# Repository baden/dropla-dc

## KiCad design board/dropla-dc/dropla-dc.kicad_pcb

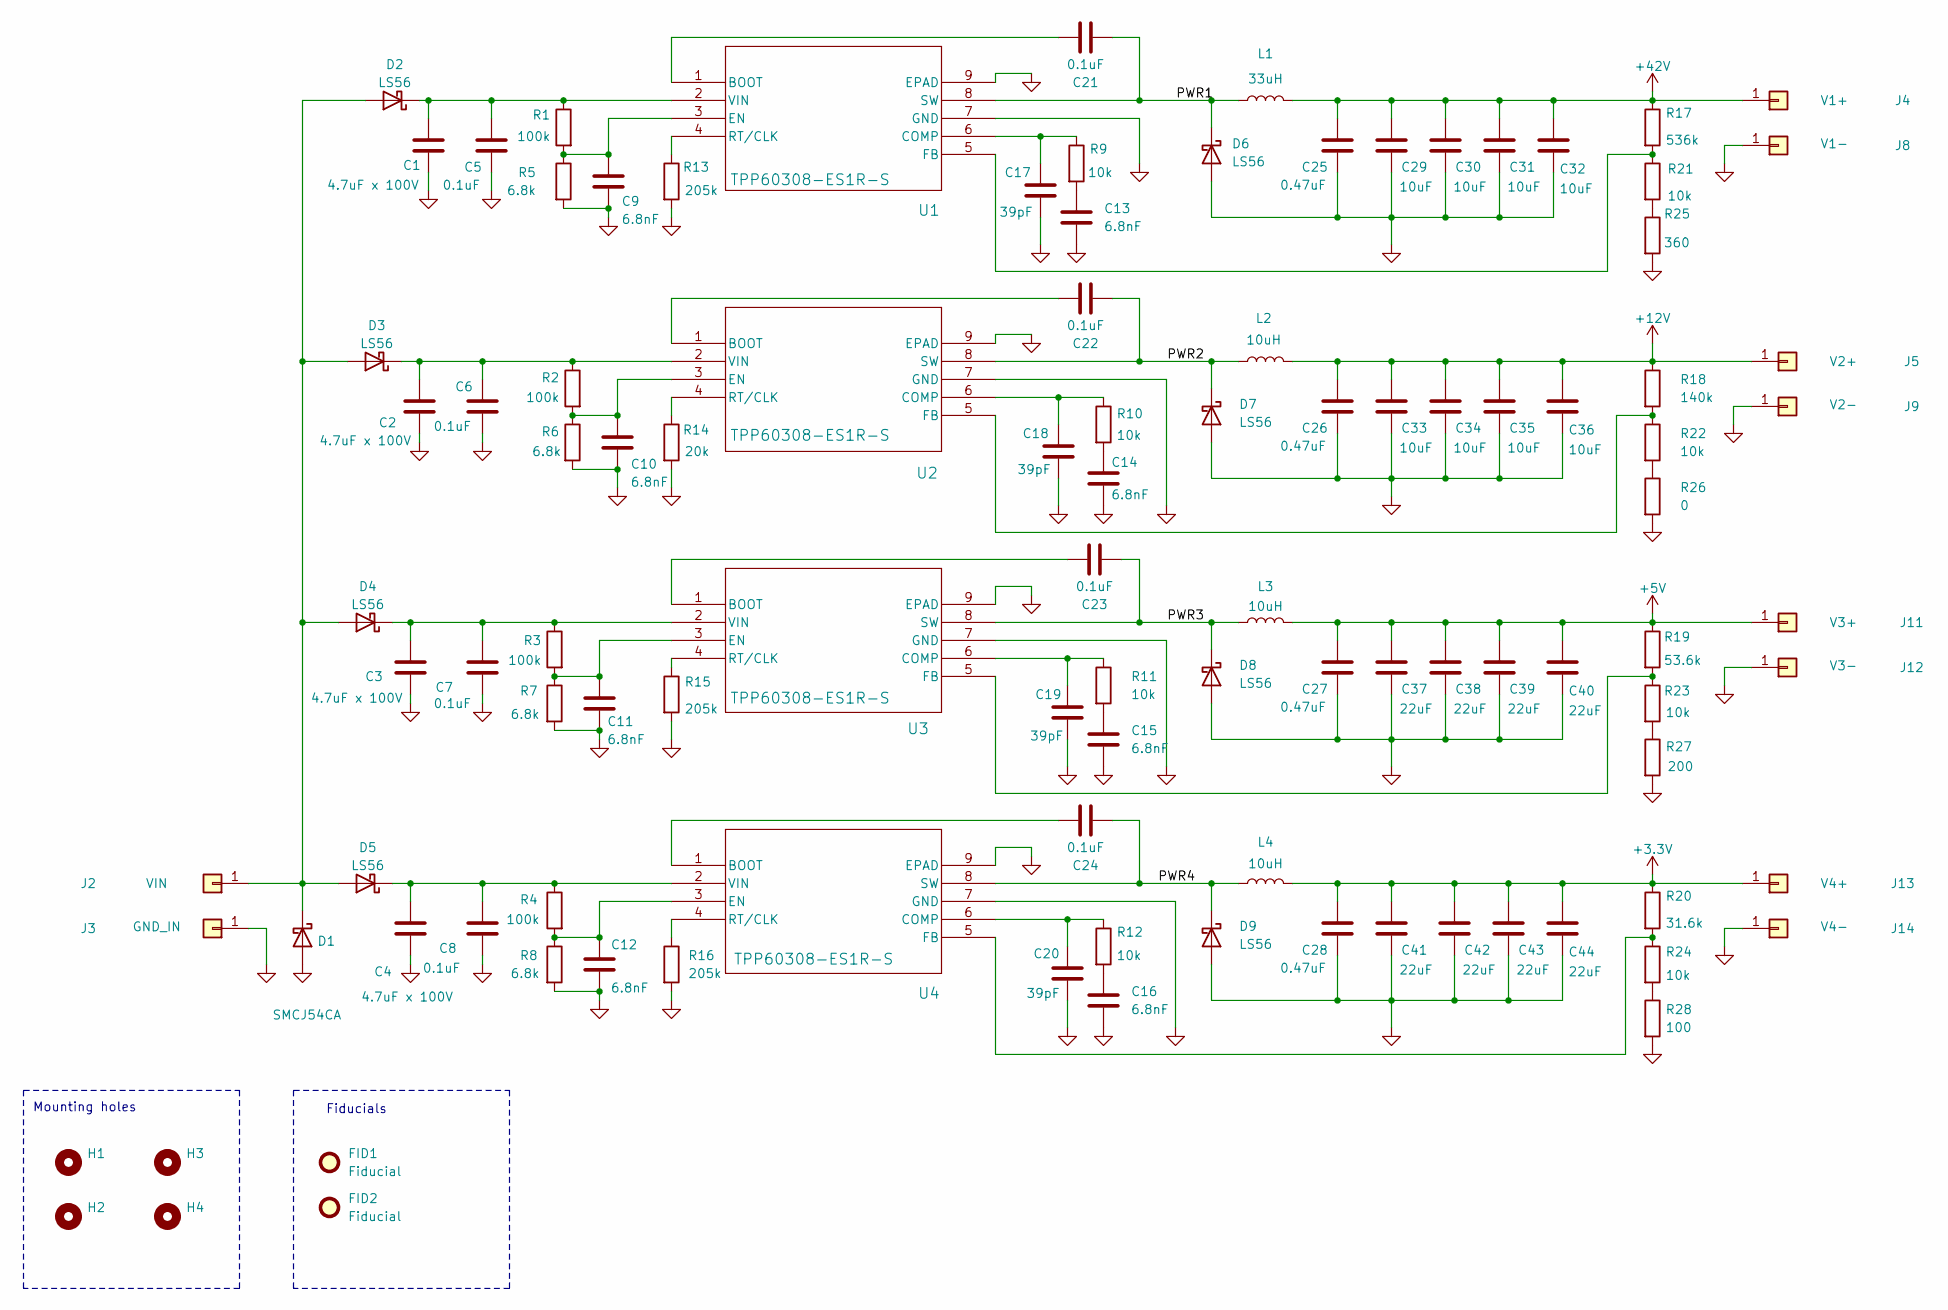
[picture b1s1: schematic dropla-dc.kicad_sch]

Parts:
C1, C2, C3, C4: 4.7uF x 100V; C_1210_3225Metric
C5, C6, C7, C8, C21, C22, C23, C24: 0.1uF; C_0603_1608Metric
C9, C10, C11, C12, C13, C14, C15, C16: 6.8nF; C_0603_1608Metric
C17, C18, C19, C20: 39pF; C_0603_1608Metric
C25, C26, C27, C28: 0.47uF; C_0603_1608Metric
C29, C30, C31, C32, C33, C34, C35, C36: 10uF; C_1206_3216Metric
C37, C38, C39, C40, C41, C42, C43, C44: 22uF; C_1206_3216Metric
D1: SMCJ54CA; D_SMC
D2, D3, D4, D5, D6, D7, D8, D9: LS56; D_SMA
FID1, FID2: Fiducial; Fiducial_1mm_Mask3mm
H1, H2, H3, H4: MountingHole; MountingHole_3.2mm_M3_DIN965
J2: VIN; Pin_D1.1mm_L8.5mm_W2.5mm_FlatFork
J3: GND_IN; Pin_D1.1mm_L8.5mm_W2.5mm_FlatFork
J4: V1+; Pin_D1.1mm_L8.5mm_W2.5mm_FlatFork
J5: V2+; Pin_D1.1mm_L8.5mm_W2.5mm_FlatFork
J8: V1-; Pin_D1.1mm_L8.5mm_W2.5mm_FlatFork
J9: V2-; Pin_D1.1mm_L8.5mm_W2.5mm_FlatFork
J11: V3+; Pin_D1.1mm_L8.5mm_W2.5mm_FlatFork
J12: V3-; Pin_D1.1mm_L8.5mm_W2.5mm_FlatFork
J13: V4+; Pin_D1.1mm_L8.5mm_W2.5mm_FlatFork
J14: V4-; Pin_D1.1mm_L8.5mm_W2.5mm_FlatFork
L1: 33uH; L_TechFuse_SL1040
L2, L3, L4: 10uH; L_Coilcraft_XAL7030-472
R1, R2, R3, R4: 100k; R_0603_1608Metric
R5, R6, R7, R8: 6.8k; R_0603_1608Metric
R9, R10, R11, R12, R21, R22, R23, R24: 10k; R_0603_1608Metric
R13, R15, R16: 205k; R_0603_1608Metric
R14: 20k; R_0603_1608Metric
R17: 536k; R_0603_1608Metric
R18: 140k; R_0603_1608Metric
R19: 53.6k; R_0603_1608Metric
R20: 31.6k; R_0603_1608Metric
R25: 360; R_0603_1608Metric
R26: 0; R_0603_1608Metric
R27: 200; R_0603_1608Metric
R28: 100; R_0603_1608Metric
U1, U2, U3, U4: TPP60308-ES1R-S; SOIC-8-1EP_3.9x4.9mm_P1.27mm_EP2.29x3mm_ThermalVias

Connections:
+3.3V: C28.2, C41.1, C42.1, C43.1, C44.1, J13.1 (Pin_1_1), L4.2, R20.1
+5V: C27.2, C37.1, C38.1, C39.1, C40.1, J11.1 (Pin_1_1), L3.2, R19.1
+12V: C26.2, C33.1, C34.1, C35.1, C36.1, J5.1 (Pin_1_1), L2.2, R18.1
+42V: C25.2, C29.1, C30.1, C31.1, C32.1, J4.1 (Pin_1_1), L1.2, R17.1
/PWR1: C21.2, D6.1 (K), L1.1, U1.8 (SW)
/PWR2: C22.2, D7.1 (K), L2.1, U2.8 (SW)
/PWR3: C23.2, D8.1 (K), L3.1, U3.8 (SW)
/PWR4: C24.2, D9.1 (K), L4.1, U4.8 (SW)
GND: C1.2, C2.2, C3.2, C4.2, C5.1, C6.1, C7.1, C8.1, C9.1, C10.1, C11.1, C12.1, C13.1, C14.1, C15.1, C16.1, C17.1, C18.1, C19.1, C20.1, C25.1, C26.1, C27.1, C28.1, C29.2, C30.2, C31.2, C32.2, C33.2, C34.2, C35.2, C36.2, C37.2, C38.2, C39.2, C40.2, C41.2, C42.2, C43.2, C44.2, D1.2 (A), D6.2 (A), D7.2 (A), D8.2 (A), D9.2 (A), J3.1 (Pin_1_1), J8.1 (Pin_1_1), J9.1 (Pin_1_1), J12.1 (Pin_1_1), J14.1 (Pin_1_1), R5.2, R6.2, R7.2, R8.2, R13.2, R14.2, R15.2, R16.2, R25.2, R26.2, R27.2, R28.2, U1.7 (GND), U1.9 (EPAD), U2.7 (GND), U2.9 (EPAD), U3.7 (GND), U3.9 (EPAD), U4.7 (GND), U4.9 (EPAD)
unnamed: C13.2, R9.2
unnamed: C14.2, R10.2
unnamed: C15.2, R11.2
unnamed: C16.2, R12.2
unnamed: D1.1 (K), D2.2 (A), D3.2 (A), D4.2 (A), D5.2 (A), J2.1 (Pin_1_1)
unnamed: C1.1, C5.2, D2.1 (K), R1.1, U1.2 (VIN)
unnamed: C2.1, C6.2, D3.1 (K), R2.1, U2.2 (VIN)
unnamed: C3.1, C7.2, D4.1 (K), R3.1, U3.2 (VIN)
unnamed: C4.1, C8.2, D5.1 (K), R4.1, U4.2 (VIN)
unnamed: R21.2, R25.1
unnamed: R22.2, R26.1
unnamed: R23.2, R27.1
unnamed: R24.2, R28.1
unnamed: C21.1, U1.1 (BOOT)
unnamed: C17.2, R9.1, U1.6 (COMP)
unnamed: C9.2, R1.2, R5.1, U1.3 (EN)
unnamed: R17.2, R21.1, U1.5 (FB)
unnamed: R13.1, U1.4 (RT/CLK)
unnamed: C22.1, U2.1 (BOOT)
unnamed: C18.2, R10.1, U2.6 (COMP)
unnamed: C10.2, R2.2, R6.1, U2.3 (EN)
unnamed: R18.2, R22.1, U2.5 (FB)
unnamed: R14.1, U2.4 (RT/CLK)
unnamed: C23.1, U3.1 (BOOT)
unnamed: C19.2, R11.1, U3.6 (COMP)
unnamed: C11.2, R3.2, R7.1, U3.3 (EN)
unnamed: R19.2, R23.1, U3.5 (FB)
unnamed: R15.1, U3.4 (RT/CLK)
unnamed: C24.1, U4.1 (BOOT)
unnamed: C20.2, R12.1, U4.6 (COMP)
unnamed: C12.2, R4.2, R8.1, U4.3 (EN)
unnamed: R20.2, R24.1, U4.5 (FB)
unnamed: R16.1, U4.4 (RT/CLK)

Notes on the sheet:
Mounting holes
Fiducials

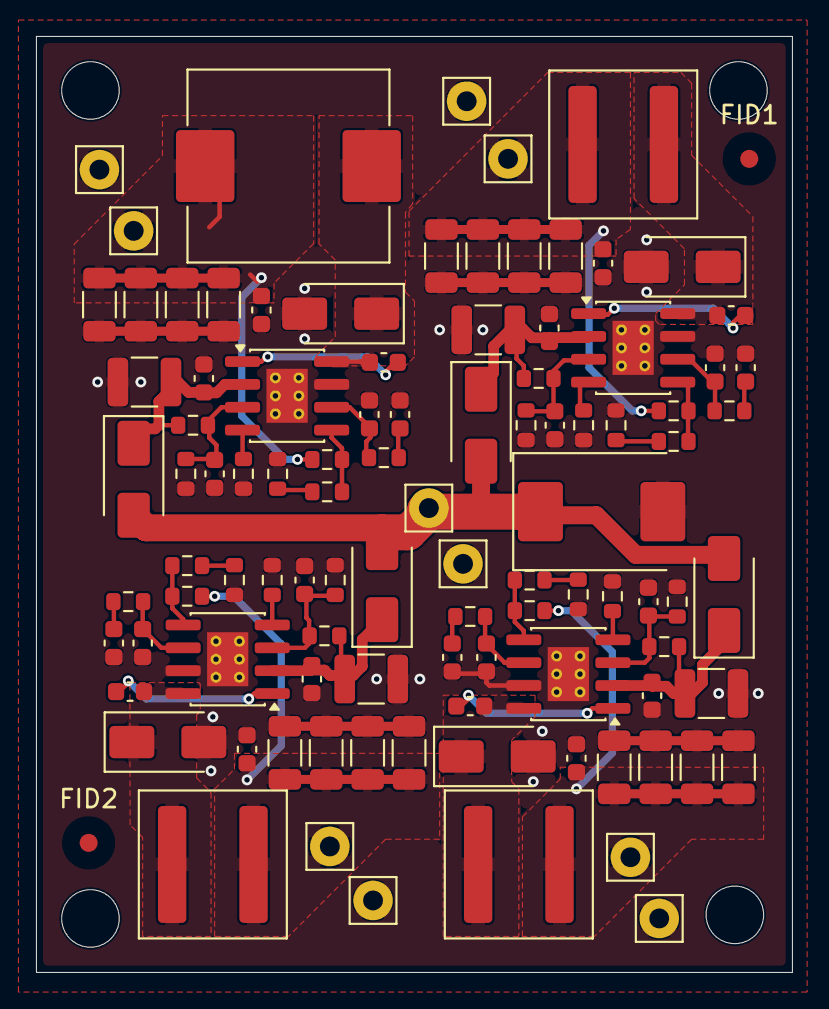
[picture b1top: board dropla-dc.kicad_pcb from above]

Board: 2 copper layers, 42.0 x 52.0 mm, 105 parts (0 on the bottom side), 42 nets.
